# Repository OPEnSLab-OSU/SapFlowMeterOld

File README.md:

# Sap Flow Meter

This is the primary location of the Sap Flow Meter project code, which is a modified code of Project LOOM code by OPEnS Lab, and PCB designs, by using EAGLE CAD PCB designing tool.

## Table of Contents
1. [Introduction](#Introduction)
2. [Instructions](#Instructions)
	1. [Assembly](#Assembly)
	2. [Wiring](#Wiring)
	3. [Installation](#Installation)
3. [Contribution](#Contribution)
4. [Acknowledgements](#Acknowledgements)

---
# Introduction
The OPENs Sapflow sensor is composed of three components, the heater probe, sensors probe, and the logging core. Depending on sensing method you choose to use (HRM or TDM) you will use two sensor probes and either one independent heater probe, or add heating elements to one of the sensor probes. These probes are then connected to the logging core, which controls the heating pulses, and reads the sensor values after a sufficient amount of time has passed, allowing the heat pulse to travel either aided or hindered by the sap flowing through the tree. Depending on how long it takes for the heat to travel, you can mathmatically determine how fast (and if using HRM, what direction) sap is flowing through the tree. 

---
# Instructions

## Assembly
[Probe Build Guide](https://github.com/OPEnSLab-OSU/SapFlowMeter/wiki/Build-Guide)

## Wiring
Connect everything as shown

## Installation
How to put it in a tree

---
# Contribution
Special thanks to...

---
# Acknowledgements

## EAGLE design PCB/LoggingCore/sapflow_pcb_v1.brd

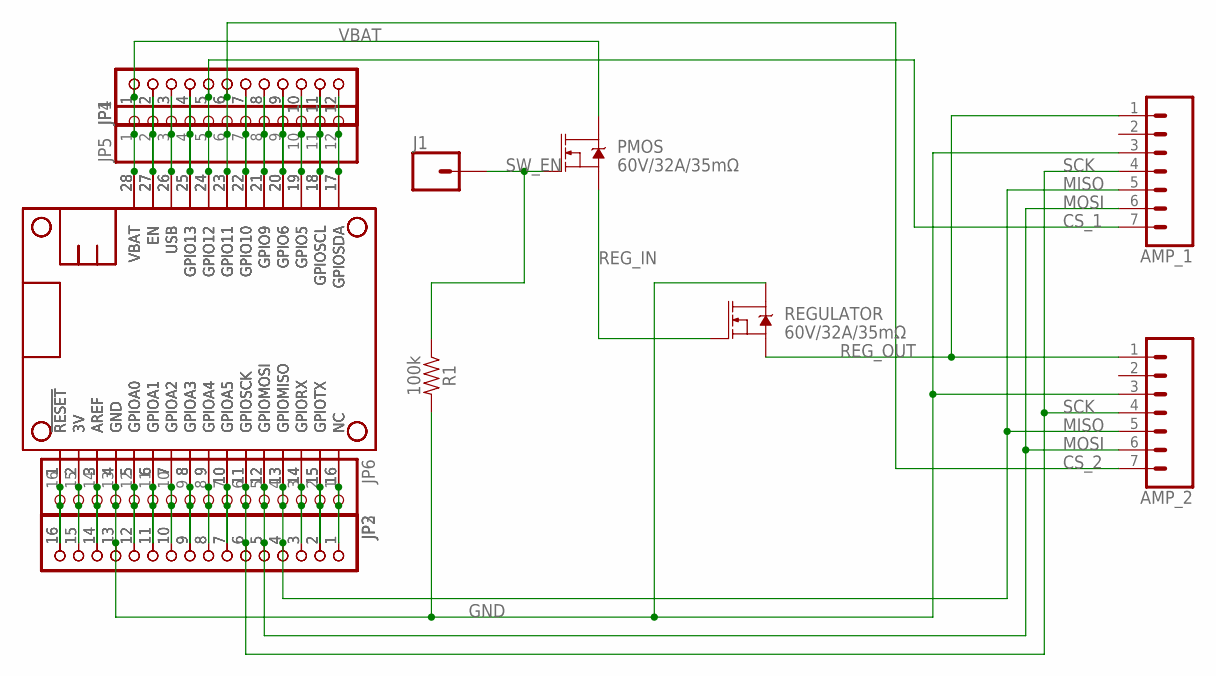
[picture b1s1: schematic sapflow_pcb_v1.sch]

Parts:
AMP_1, AMP_2: CONN_07; 1X07
J1: CONN_01; 1X01
JP1, JP4, JP5: HEADER-1X1276MIL; 1X12_ROUND_76MIL
JP2, JP3, JP6: HEADER-1X16_76MIL; 1X16_ROUND_76MIL
MS1, MS2, MS3: FEATHERWING_NODIM; FEATHERWING_DIM
PMOS: 60V/32A/35mΩ; TO220V
R1: 100k; AXIAL-0.3
REGULATOR: 60V/32A/35mΩ; TO220V

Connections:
3V: JP2.15, JP3.15, JP6.15, MS1.2 (3V), MS2.2 (3V), MS3.2 (3V)
A: JP2.12, JP3.12, JP6.12, MS1.5 (GPIOA0), MS2.5 (GPIOA0), MS3.5 (GPIOA0)
AREF: JP2.14, JP3.14, JP6.14, MS1.3 (AREF), MS2.3 (AREF), MS3.3 (AREF)
B: JP2.11, JP3.11, JP6.11, MS1.6 (GPIOA1), MS2.6 (GPIOA1), MS3.6 (GPIOA1)
C: JP2.10, JP3.10, JP6.10, MS1.7 (GPIOA2), MS2.7 (GPIOA2), MS3.7 (GPIOA2)
CS_1: AMP_1.7, JP1.5, JP4.5, JP5.5, MS1.24 (GPIO12), MS2.24 (GPIO12), MS3.24 (GPIO12)
CS_2: AMP_2.7, JP1.6, JP4.6, JP5.6, MS1.23 (GPIO11), MS2.23 (GPIO11), MS3.23 (GPIO11)
D: JP2.9, JP3.9, JP6.9, MS1.8 (GPIOA3), MS2.8 (GPIOA3), MS3.8 (GPIOA3)
E: JP2.8, JP3.8, JP6.8, MS1.9 (GPIOA4), MS2.9 (GPIOA4), MS3.9 (GPIOA4)
EN: JP1.2, JP4.2, JP5.2, MS1.27 (EN), MS2.27 (EN), MS3.27 (EN)
F: JP2.7, JP3.7, JP6.7, MS1.10 (GPIOA5), MS2.10 (GPIOA5), MS3.10 (GPIOA5)
G: JP2.1, JP3.1, JP6.1, MS1.16 (NC), MS2.16 (NC), MS3.16 (NC)
GND: AMP_1.3, AMP_2.3, JP2.13, JP3.13, JP6.13, MS1.4 (GND), MS2.4 (GND), MS3.4 (GND), R1.P$2 (2), REGULATOR.2 (D)
I: JP1.9, JP4.9, JP5.9, MS1.20 (GPIO6), MS2.20 (GPIO6), MS3.20 (GPIO6)
J: JP1.10, JP4.10, JP5.10, MS1.19 (GPIO5), MS2.19 (GPIO5), MS3.19 (GPIO5)
K: JP1.8, JP4.8, JP5.8, MS1.21 (GPIO9), MS2.21 (GPIO9), MS3.21 (GPIO9)
L: JP1.7, JP4.7, JP5.7, MS1.22 (GPIO10), MS2.22 (GPIO10), MS3.22 (GPIO10)
MISO: AMP_1.5, AMP_2.5, JP2.4, JP3.4, JP6.4, MS1.13 (GPIOMISO), MS2.13 (GPIOMISO), MS3.13 (GPIOMISO)
MOSI: AMP_1.6, AMP_2.6, JP2.5, JP3.5, JP6.5, MS1.12 (GPIOMOSI), MS2.12 (GPIOMOSI), MS3.12 (GPIOMOSI)
O: JP1.4, JP4.4, JP5.4, MS1.25 (GPIO13), MS2.25 (GPIO13), MS3.25 (GPIO13)
REG_IN: PMOS.3 (S), REGULATOR.1 (G)
REG_OUT: AMP_1.1, AMP_2.1, REGULATOR.3 (S)
RESET: JP2.16, JP3.16, JP6.16, MS1.1 (!RESET), MS2.1 (!RESET), MS3.1 (!RESET)
RX: JP2.3, JP3.3, JP6.3, MS1.14 (GPIORX), MS2.14 (GPIORX), MS3.14 (GPIORX)
SCK: AMP_1.4, AMP_2.4, JP2.6, JP3.6, JP6.6, MS1.11 (GPIOSCK), MS2.11 (GPIOSCK), MS3.11 (GPIOSCK)
SCL: JP1.11, JP4.11, JP5.11, MS1.18 (GPIOSCL), MS2.18 (GPIOSCL), MS3.18 (GPIOSCL)
SDA: JP1.12, JP4.12, JP5.12, MS1.17 (GPIOSDA), MS2.17 (GPIOSDA), MS3.17 (GPIOSDA)
SW_EN: J1.1, PMOS.1 (G), R1.P$1 (1)
TX: JP2.2, JP3.2, JP6.2, MS1.15 (GPIOTX), MS2.15 (GPIOTX), MS3.15 (GPIOTX)
USB: JP1.3, JP4.3, JP5.3, MS1.26 (USB), MS2.26 (USB), MS3.26 (USB)
VBAT: JP1.1, JP4.1, JP5.1, MS1.28 (VBAT), MS2.28 (VBAT), MS3.28 (VBAT), PMOS.2 (D)

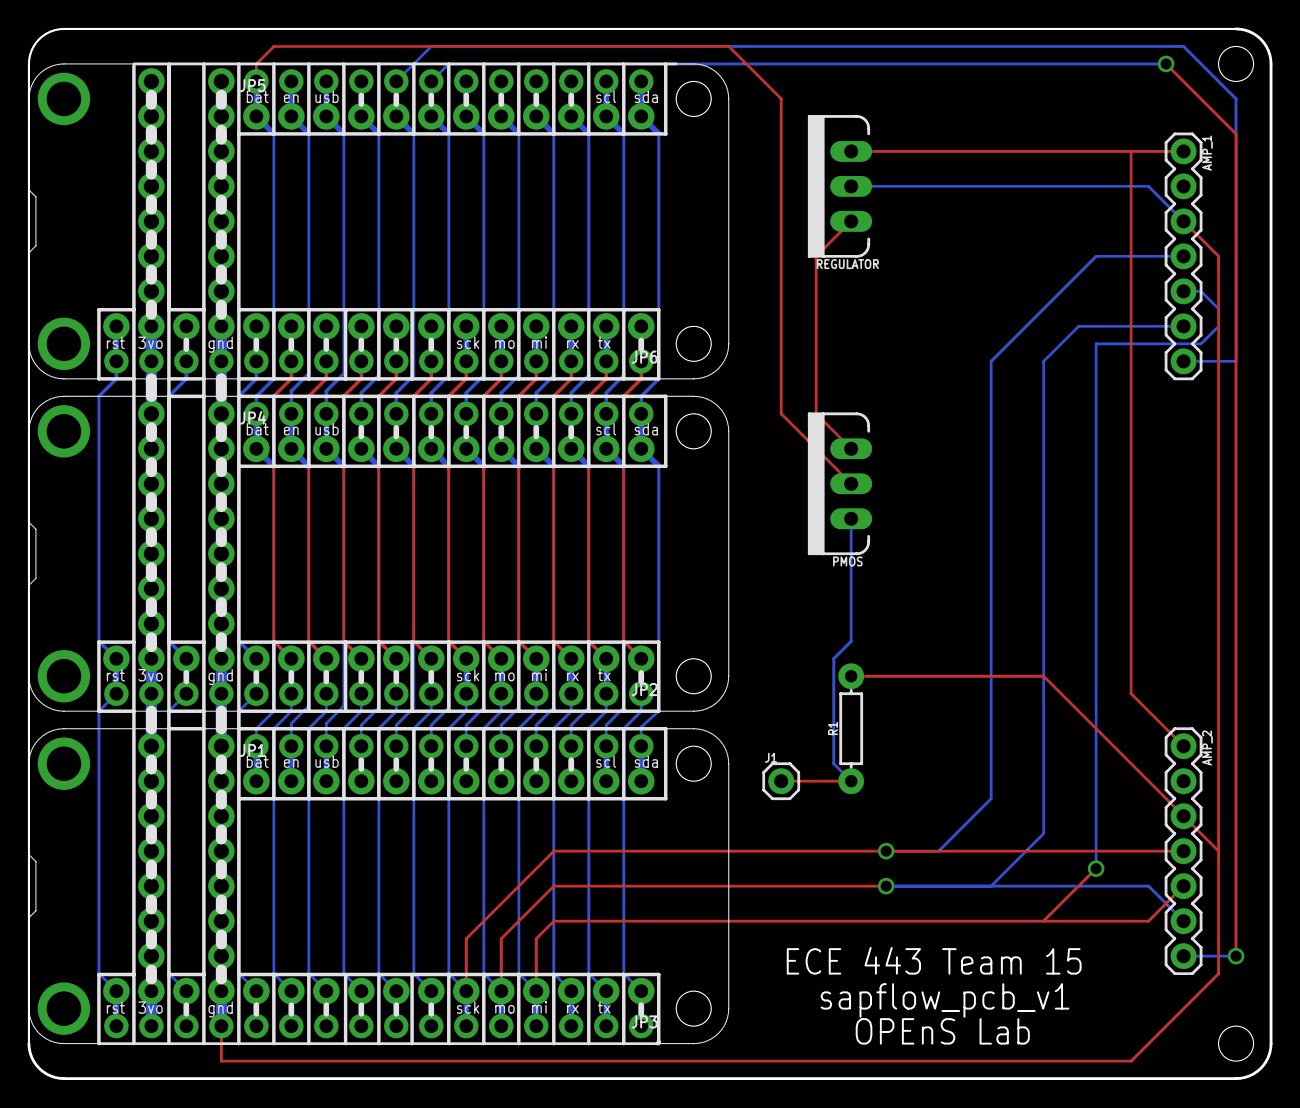
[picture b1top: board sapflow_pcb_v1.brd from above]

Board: 2 copper layers, 90.2 x 76.2 mm, 15 parts (0 on the bottom side), 31 nets.

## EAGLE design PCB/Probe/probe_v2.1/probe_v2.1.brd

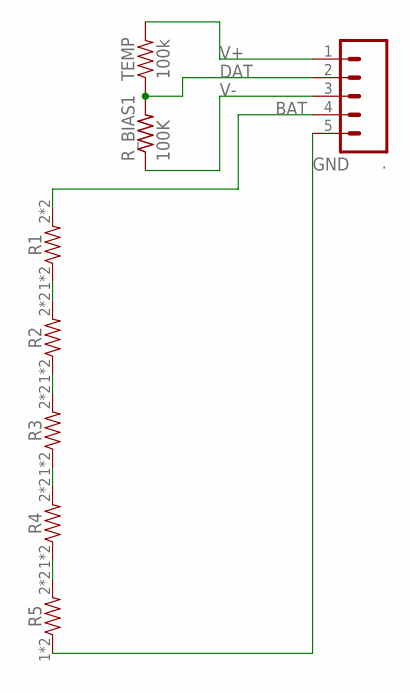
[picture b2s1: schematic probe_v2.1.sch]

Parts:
.: CONN_05NO_SILK; 1X05_NO_SILK
R1, R2, R3, R4, R5: DRES; 0603
R_BIAS1: 100K; 0805-THM
TEMP: 100k; 0603

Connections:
BAT: ..4, R1.2, R1.P$2 (2)
DAT: ..2, R_BIAS1.2, TEMP.1
GND: ..5, R5.1, R5.P$1 (1)
unnamed: R2.1, R2.P$1 (1), R3.2, R3.P$2 (2)
unnamed: R1.1, R1.P$1 (1), R2.2, R2.P$2 (2)
unnamed: R3.1, R3.P$1 (1), R4.2, R4.P$2 (2)
unnamed: R4.1, R4.P$1 (1), R5.2, R5.P$2 (2)
V+: ..1, TEMP.2
V-: ..3, R_BIAS1.1

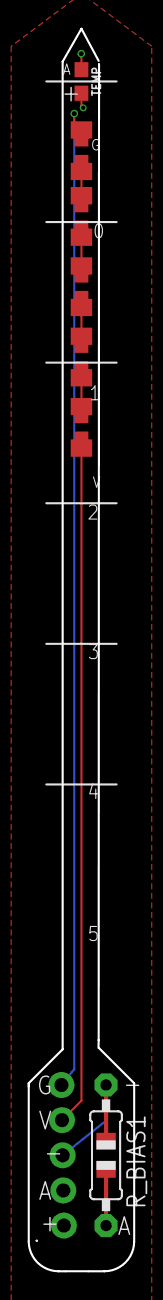
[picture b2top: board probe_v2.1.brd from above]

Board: 4 copper layers, 7.6 x 89.8 mm, 8 parts (0 on the bottom side), 9 nets.

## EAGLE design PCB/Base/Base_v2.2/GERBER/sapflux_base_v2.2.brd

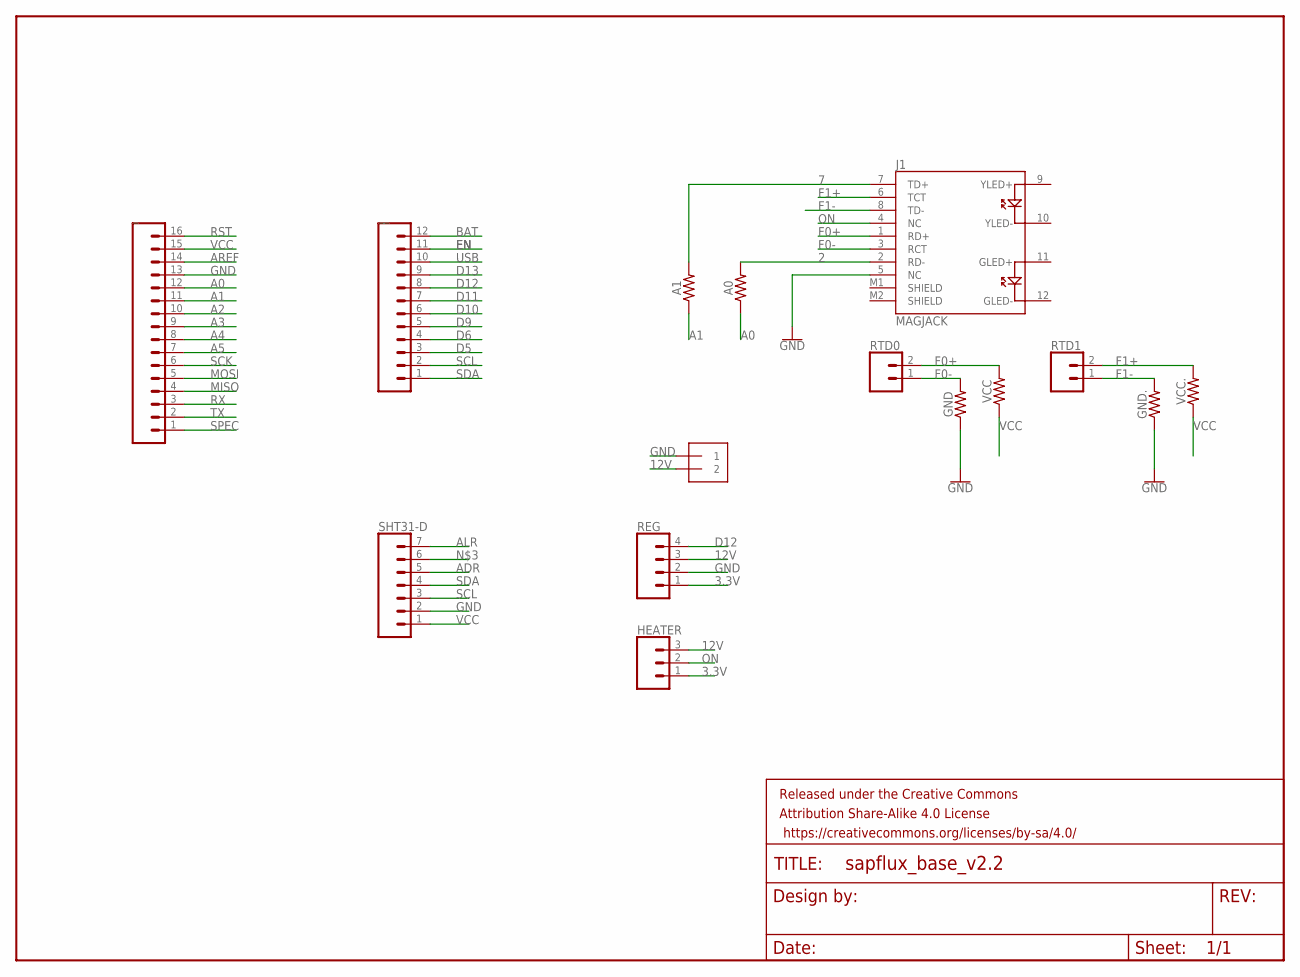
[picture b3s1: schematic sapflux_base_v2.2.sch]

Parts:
.: 1X2-3.5MM
A0, A1: 1.8MOHM; 0603
FRAME1: FRAME-LETTER; CREATIVE_COMMONS
GND, GND.: 1.8MOHM; 0603
HEATER: CONN_03; 1X03
J1: MAGJACK
REG: CONN_04; 1X04
RTD0, RTD1: CONN_02; 1X02
SHT31-D: CONN_07; 1X07
VCC, VCC.: 1.8MOHM; 0603
_: CONN_16; 1X16
__: CONN_12; 1X12

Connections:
2: A0.2, J1.2 (RD-)
3.3V: HEATER.1, REG.1
7: A1.2, J1.7 (TD+)
12V: ..2, HEATER.3, REG.3
A0: A0.1, _.12
A1: A1.1, _.11
A2: _.10
A3: _.9
A4: _.8
A5: _.7
ADR: SHT31-D.5
ALR: SHT31-D.7
AREF: _.14
BAT: __.12
D5: __.3
D6: __.4
D9: __.5
D10: __.6
D11: __.7
D12: REG.4, __.8
D13: __.9
EN: __.11
F0+: J1.1 (RD+), RTD0.2, VCC.2
F0-: GND.2, J1.3 (RCT), RTD0.1
F1+: J1.6 (TCT), RTD1.2, VCC..2
F1-: GND..2, J1.8 (TD-), RTD1.1
GND: ..1, GND.1, GND..1, J1.5 (NC), REG.2, SHT31-D.2, _.13
MISO: _.4
MOSI: _.5
ON: HEATER.2, J1.4 (NC)
RST: _.16
RX: _.3
SCK: _.6
SCL: SHT31-D.3, __.2
SDA: SHT31-D.4, __.1
SPEC: _.1
TX: _.2
USB: __.10
VCC: SHT31-D.1, VCC.1, VCC..1, _.15

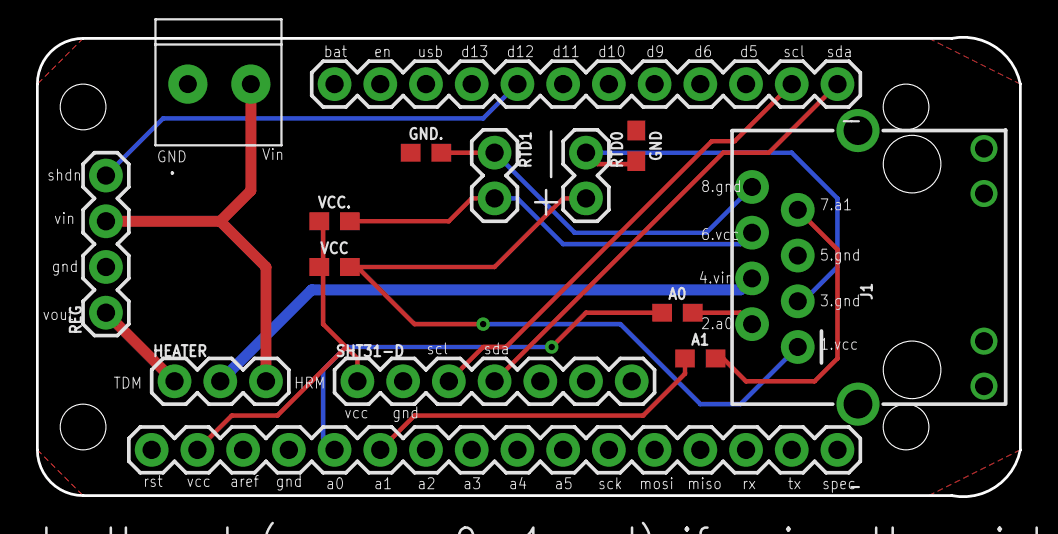
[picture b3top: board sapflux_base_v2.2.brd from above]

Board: 2 copper layers, 54.6 x 25.5 mm, 16 parts (0 on the bottom side), 16 nets.

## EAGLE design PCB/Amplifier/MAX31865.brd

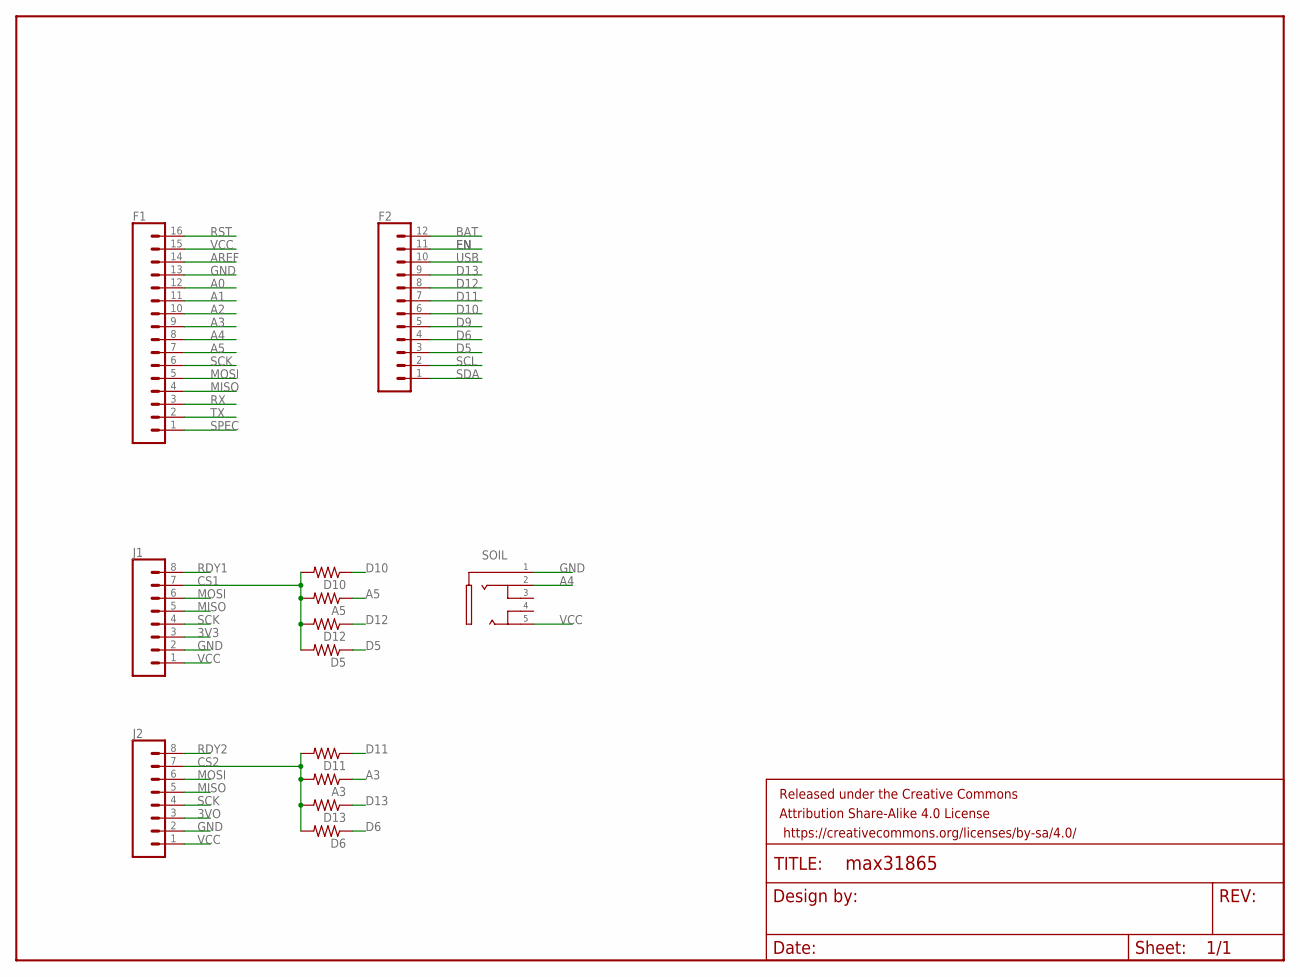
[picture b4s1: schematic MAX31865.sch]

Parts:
A3, A5: R-US_R0603; R0603
D5, D6, D10, D11, D12, D13: R-US_R0603; R0603
F1: CONN_16; 1X16
F2: CONN_12; 1X12
FRAME1: FRAME-LETTER; CREATIVE_COMMONS
J1, J2: CONN_08"; 1X08
SOIL: JW-PJ-307-5H

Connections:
3V3: J1.3
3VO: J2.3
A0: F1.12
A1: F1.11
A2: F1.10
A3: A3.1, F1.9
A4: F1.8, SOIL.2
A5: A5.1, F1.7
AREF: F1.14
BAT: F2.12
CS1: A5.2, D5.2, D10.2, D12.2, J1.7
CS2: A3.2, D6.2, D11.2, D13.2, J2.7
D5: D5.1, F2.3
D6: D6.1, F2.4
D9: F2.5
D10: D10.1, F2.6
D11: D11.1, F2.7
D12: D12.1, F2.8
D13: D13.1, F2.9
EN: F2.11
GND: F1.13, J1.2, J2.2, SOIL.1
MISO: F1.4, J1.5, J2.5
MOSI: F1.5, J1.6, J2.6
RDY1: J1.8
RDY2: J2.8
RST: F1.16
RX: F1.3
SCK: F1.6, J1.4, J2.4
SCL: F2.2
SDA: F2.1
SPEC: F1.1
TX: F1.2
USB: F2.10
VCC: F1.15, J1.1, J2.1, SOIL.5

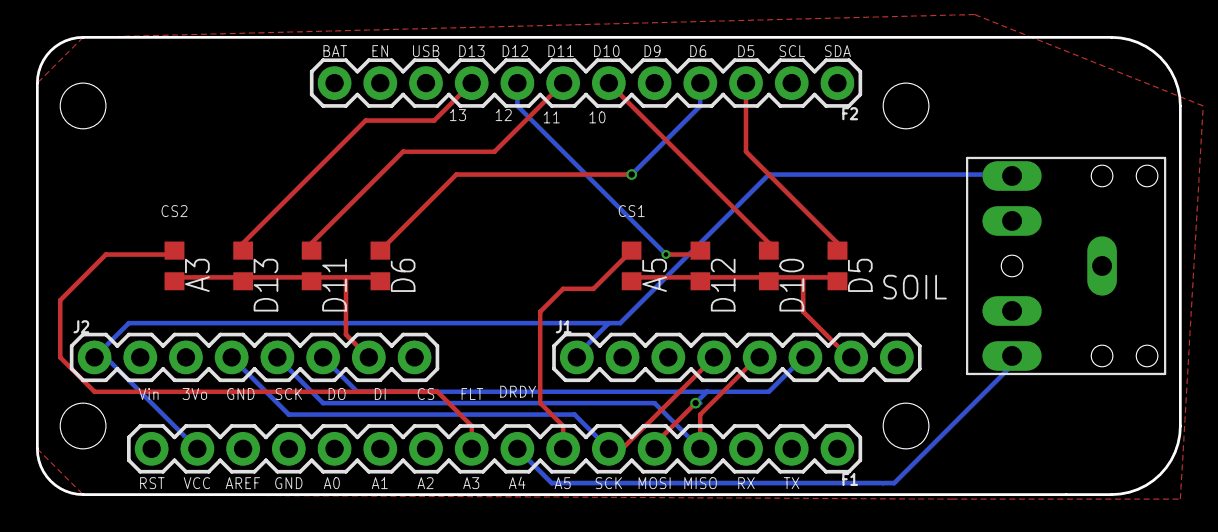
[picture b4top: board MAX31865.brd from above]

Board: 2 copper layers, 63.5 x 25.4 mm, 14 parts (0 on the bottom side), 16 nets.

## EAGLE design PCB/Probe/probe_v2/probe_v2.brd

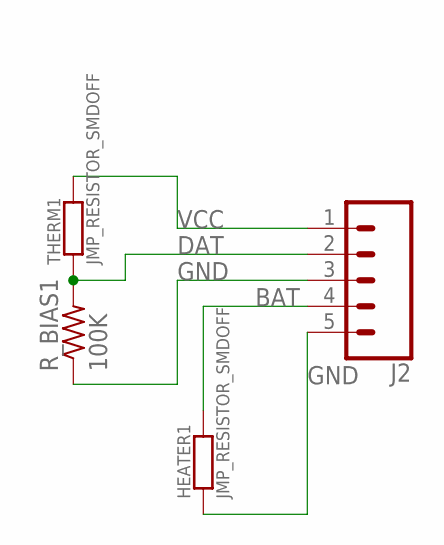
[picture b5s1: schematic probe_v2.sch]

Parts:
HEATER1: JMP_RESISTOR_SMDOFF; JMP_OFF_SMD
J2: CONN_05NO_SILK; 1X05_NO_SILK
R_BIAS1: 100K; 0805-THM
THERM1: JMP_RESISTOR_SMDOFF; JMP_OFF_SMD

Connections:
BAT: HEATER1.2, J2.4
DAT: J2.2, R_BIAS1.2, THERM1.1
GND: HEATER1.1, J2.3, J2.5, R_BIAS1.1
VCC: J2.1, THERM1.2

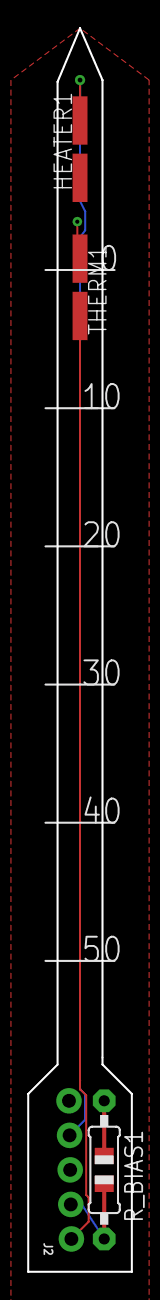
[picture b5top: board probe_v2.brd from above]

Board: 4 copper layers, 7.6 x 91.4 mm, 4 parts (0 on the bottom side), 4 nets.

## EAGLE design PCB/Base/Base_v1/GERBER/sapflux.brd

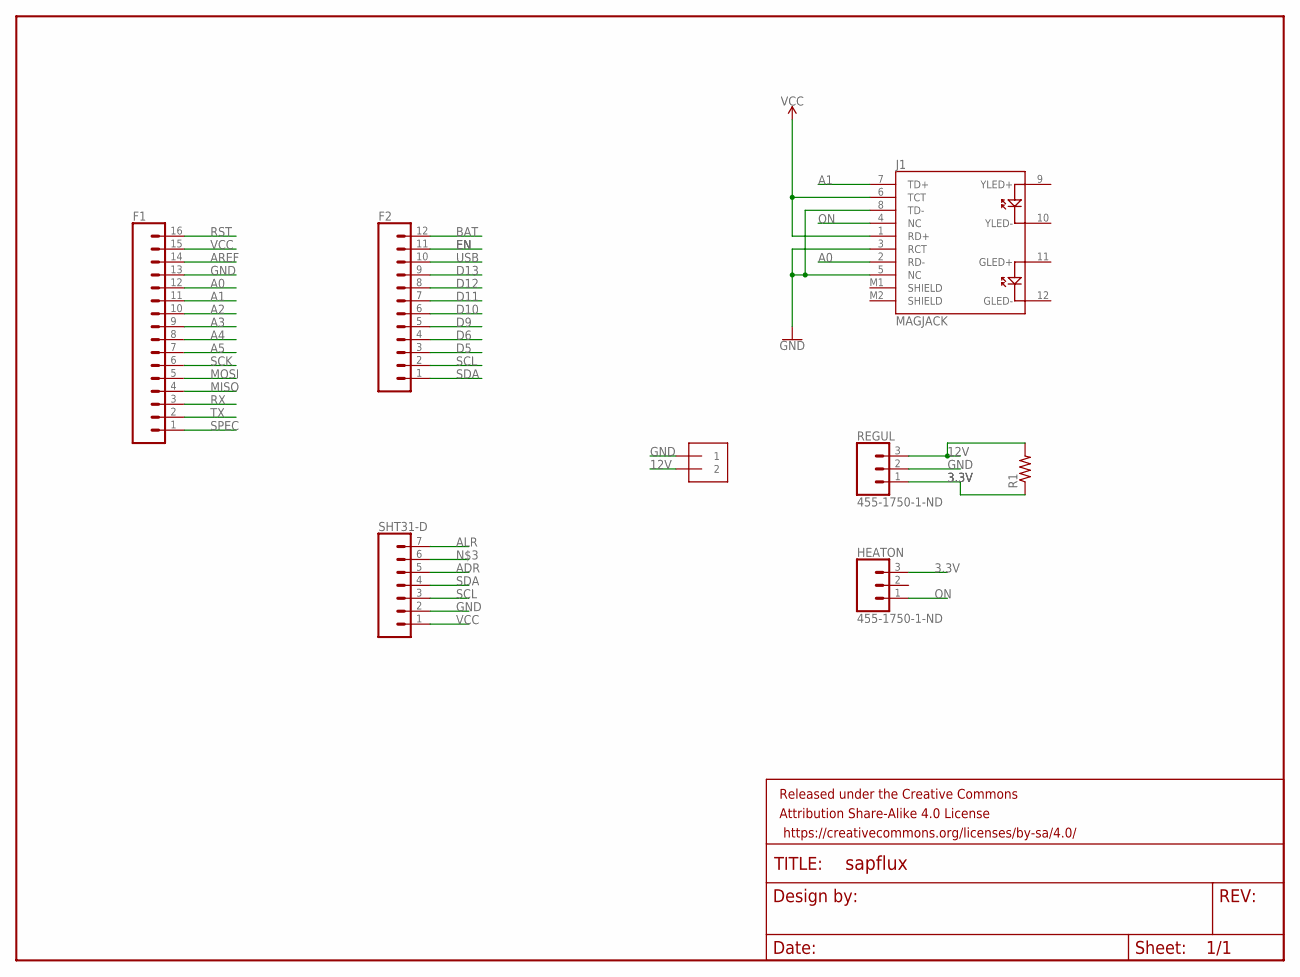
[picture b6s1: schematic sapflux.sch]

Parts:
F1: CONN_16; 1X16
F2: CONN_12; 1X12
FRAME1: FRAME-LETTER; CREATIVE_COMMONS
HEATON: 455-1750-1-ND; 1X03
J1: MAGJACK
J2: 1X2-3.5MM
R1: R-US_R0603; R0603
REGUL: 455-1750-1-ND; 1X03
SHT31-D: CONN_07; 1X07

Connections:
3.3V: HEATON.3, R1.1, REGUL.1
12V: J2.2, R1.2, REGUL.3
A0: F1.12, J1.2 (RD-)
A1: F1.11, J1.7 (TD+)
A2: F1.10
A3: F1.9
A4: F1.8
A5: F1.7
ADR: SHT31-D.5
ALR: SHT31-D.7
AREF: F1.14
BAT: F2.12
D5: F2.3
D6: F2.4
D9: F2.5
D10: F2.6
D11: F2.7
D12: F2.8
D13: F2.9
EN: F2.11
GND: F1.13, J1.3 (RCT), J1.5 (NC), J1.8 (TD-), J2.1, REGUL.2, SHT31-D.2
MISO: F1.4
MOSI: F1.5
ON: HEATON.1, J1.4 (NC)
RST: F1.16
RX: F1.3
SCK: F1.6
SCL: F2.2, SHT31-D.3
SDA: F2.1, SHT31-D.4
SPEC: F1.1
TX: F1.2
USB: F2.10
VCC: F1.15, J1.1 (RD+), J1.6 (TCT), SHT31-D.1

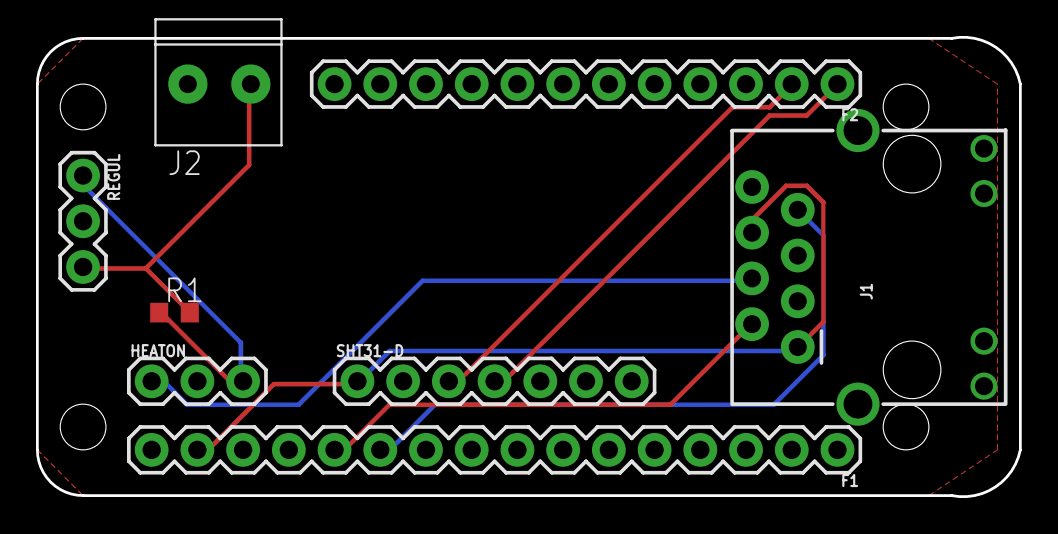
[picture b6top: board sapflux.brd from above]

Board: 2 copper layers, 54.6 x 25.5 mm, 9 parts (0 on the bottom side), 9 nets.

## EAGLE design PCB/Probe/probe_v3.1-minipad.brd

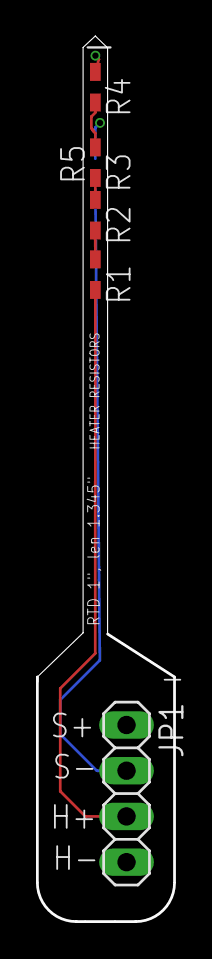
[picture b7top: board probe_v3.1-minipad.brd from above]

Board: 4 copper layers, 7.6 x 49.1 mm, 6 parts (0 on the bottom side), 7 nets.

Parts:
JP1: 1X04
R1, R2, R3, R4: R0603
R5: R0603-BOTTOM

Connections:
BAT: JP1.3, R1.2
DAT: JP1.2, R5.1
GND: JP1.4, R4.1
unnamed: R1.1, R2.2
unnamed: R2.1, R3.2
unnamed: R3.1, R4.2
V+: JP1.1, R5.2

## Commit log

2018-08-08 Add all code files
2018-08-08 Add PCB files
2018-08-08 add cad files
2018-08-16 fix minor error
2018-09-17 Update all of files
2018-09-19 Fix PCB GERBER
2018-10-13 Add MAX31865 functionality
2018-10-16 Hardware SPI doesn't work with other SPI deivce
2018-10-16 RTD Calibration code
2018-10-16 Combine RTD code and ordinary sapflow code
2018-10-19 Update README.md
    Add config.h description of HUB
2018-10-19 Update README.md
    Add NODE description of config.h.
2018-10-22 modified definition
2019-01-10 Add Load cell code
2019-01-10 Add wiring pictures
2019-06-03 Removed .DS_store from Repo
    .DS_Store is the desktop configuration file for OSX systems which stores into on custom changes made to the encompassing file. This really isn't necessary so I'm dumping it.
2019-06-03 Removed all instances of .DS_Store, come on people, unstage that stuff when commiting, it just looks bad.
2019-06-03 Create .gitignore
    Added .DS_Store to gitignore to prevent future unintentional additions.
2019-07-03 Cleaning up and consolidating the log data
2019-07-03 New structure to readme
2019-07-19 Test Commit, Desregard
2019-07-19 Added assets for Build Guide
2019-07-19 Changed type to JPEG for github compatibility
2019-07-19 State of master prior to reorganizing the repo, all levacy versions of code can be found here
2019-07-19 Adding intro and linking to build guide
2019-07-19 Removing old versions, new versions to come.

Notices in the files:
parts and their libraries:
SparkFun-Connectors: Licensing: Creative Commons ShareAlike 4.0 International - https://creativecommons.org/licenses/by-sa/4.0
SparkFun-Aesthetics: Released under the Creative Commons Attribution Share-Alike 4.0 License
SparkFun-Aesthetics: https://creativecommons.org/licenses/by-sa/4.0
